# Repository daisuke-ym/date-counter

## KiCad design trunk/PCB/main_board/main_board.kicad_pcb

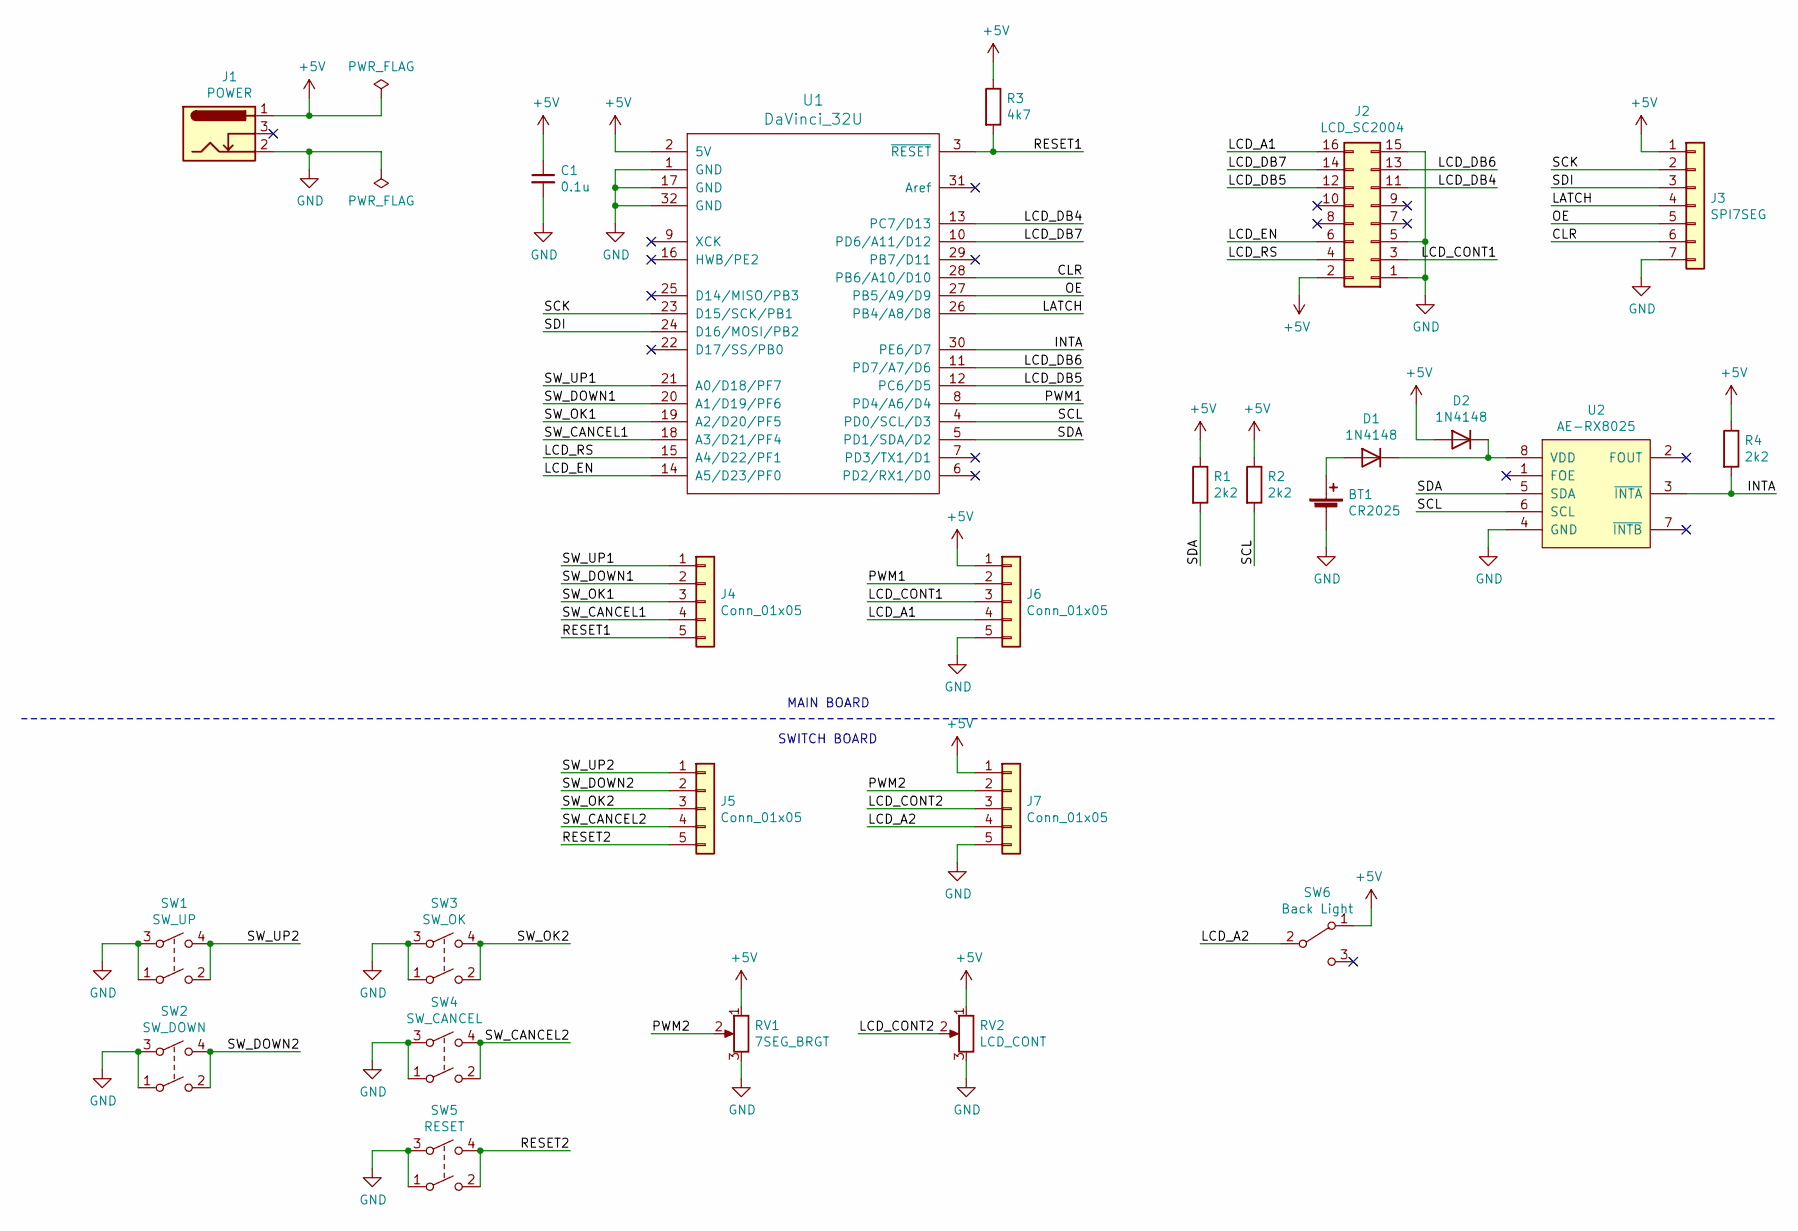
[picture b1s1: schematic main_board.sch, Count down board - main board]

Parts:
BT1: CR2025; CH25-2032LF
C1: 0.1u; C_Disc_D3.4mm_W2.1mm_P2.50mm
D1, D2: 1N4148; D_DO-15_P10.16mm_Horizontal
J1: POWER; BarrelJack_Horizontal
J2: LCD_SC2004; SC2004
J3: SPI7SEG; JST_XH_S7B-XH-A-1_1x07_P2.50mm_Horizontal
J4, J5, J6, J7: Conn_01x05; PinHeader_1x05_P2.54mm_Vertical
R1, R2, R4: 2k2; R_Axial_DIN0207_L6.3mm_D2.5mm_P10.16mm_Horizontal
R3: 4k7; R_Axial_DIN0207_L6.3mm_D2.5mm_P10.16mm_Horizontal
RV1: 7SEG_BRGT; GF063P1
RV2: LCD_CONT; GF063P1
SW1: SW_UP; TVDP01-G73AB
SW2: SW_DOWN; TVDP01-G73AB
SW3: SW_OK; TVDP01-G73AB
SW4: SW_CANCEL; TVDP01-G73AB
SW5: RESET; TVDP01-G73AB
SW6: Back Light; SS12D01G4
U1: DaVinci_32U; DIP-32_W15.24mm_Socket
U2: AE-RX8025; DIP-8_W7.62mm_Socket

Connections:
+5V: C1.1, D2.2 (A), J1.1, J2.2, J3.1, J6.1, J7.1, R1.1, R2.1, R3.1, R4.1, RV1.1, RV2.1, SW6.1 (A), U1.2 (5V)
/CLR: J3.6, U1.28 (PB6/A10/D10)
/INTA: R4.2, U1.30 (PE6/D7), U2.3 (~INTA)
/LATCH: J3.4, U1.26 (PB4/A8/D8)
/LCD_A1: J2.16, J6.4
/LCD_A2: J7.4, SW6.2 (B)
/LCD_CONT1: J2.3, J6.3
/LCD_CONT2: J7.3, RV2.2
/LCD_DB4: J2.11, U1.13 (PC7/D13)
/LCD_DB5: J2.12, U1.12 (PC6/D5)
/LCD_DB6: J2.13, U1.11 (PD7/A7/D6)
/LCD_DB7: J2.14, U1.10 (PD6/A11/D12)
/LCD_EN: J2.6, U1.14 (A5/D23/PF0)
/LCD_RS: J2.4, U1.15 (A4/D22/PF1)
/OE: J3.5, U1.27 (PB5/A9/D9)
/PWM1: J6.2, U1.8 (PD4/A6/D4)
/PWM2: J7.2, RV1.2
/RESET1: J4.5, R3.2, U1.3 (~RESET)
/RESET2: J5.5, SW5.2, SW5.4
/SCK: J3.2, U1.23 (D15/SCK/PB1)
/SCL: R2.2, U1.4 (PD0/SCL/D3), U2.6 (SCL)
/SDA: R1.2, U1.5 (PD1/SDA/D2), U2.5 (SDA)
/SDI: J3.3, U1.24 (D16/MOSI/PB2)
/SW_CANCEL1: J4.4, U1.18 (A3/D21/PF4)
/SW_CANCEL2: J5.4, SW4.2, SW4.4
/SW_DOWN1: J4.2, U1.20 (A1/D19/PF6)
/SW_DOWN2: J5.2, SW2.2, SW2.4
/SW_OK1: J4.3, U1.19 (A2/D20/PF5)
/SW_OK2: J5.3, SW3.2, SW3.4
/SW_UP1: J4.1, U1.21 (A0/D18/PF7)
/SW_UP2: J5.1, SW1.2, SW1.4
GND: BT1.2 (-), C1.2, J1.2, J2.1, J2.5, J2.15, J3.7, J6.5, J7.5, RV1.3, RV2.3, SW1.1, SW1.3, SW2.1, SW2.3, SW3.1, SW3.3, SW4.1, SW4.3, SW5.1, SW5.3, U1.1 (GND), U1.17 (GND), U1.32 (GND), U2.4 (GND)
unnamed: BT1.1 (+), D1.2 (A)
unnamed: D1.1 (K), D2.1 (K), U2.8 (VDD)

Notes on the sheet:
MAIN BOARD
SWITCH BOARD

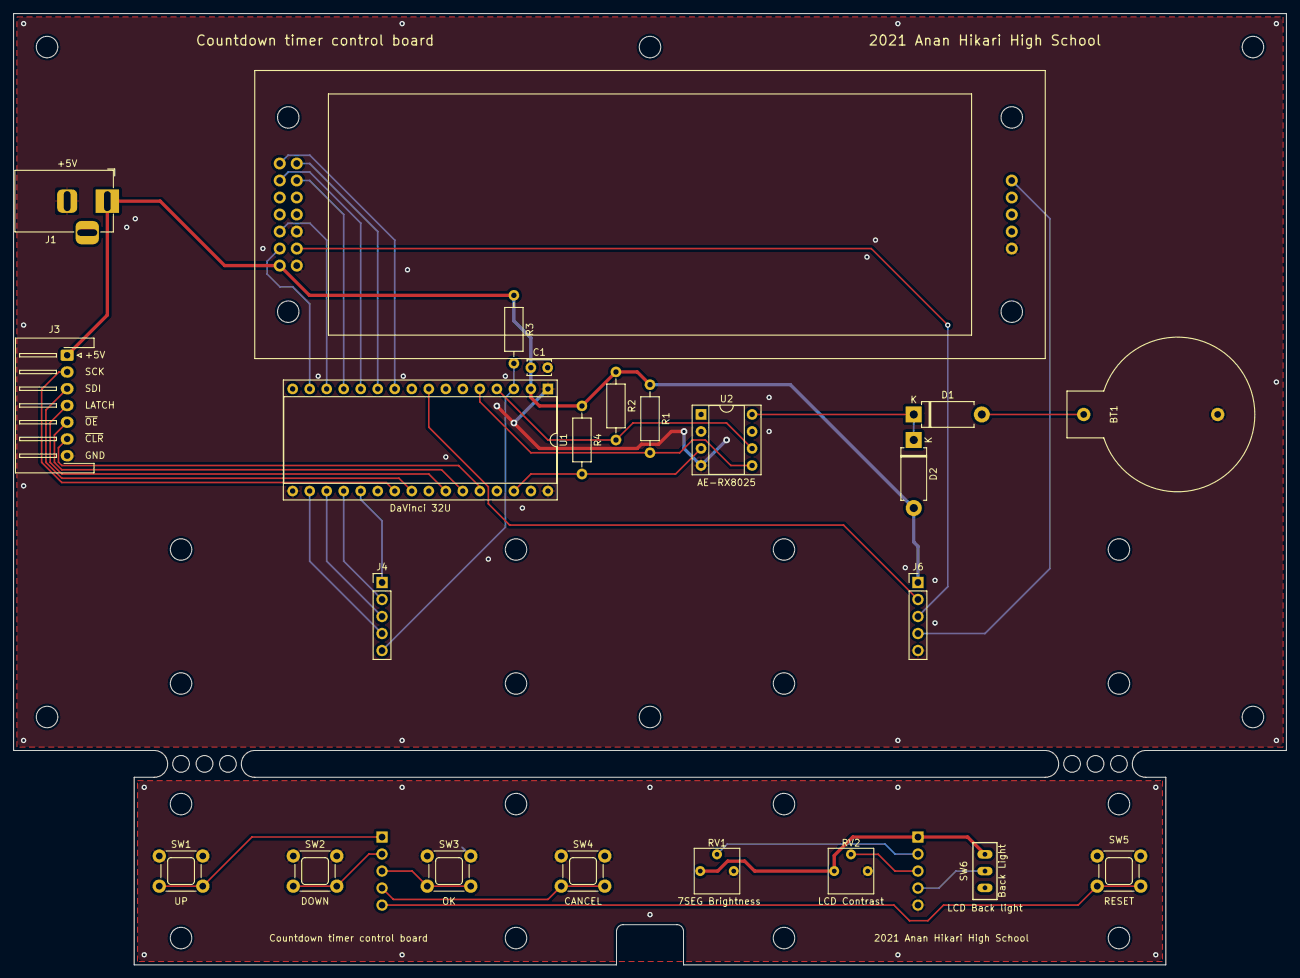
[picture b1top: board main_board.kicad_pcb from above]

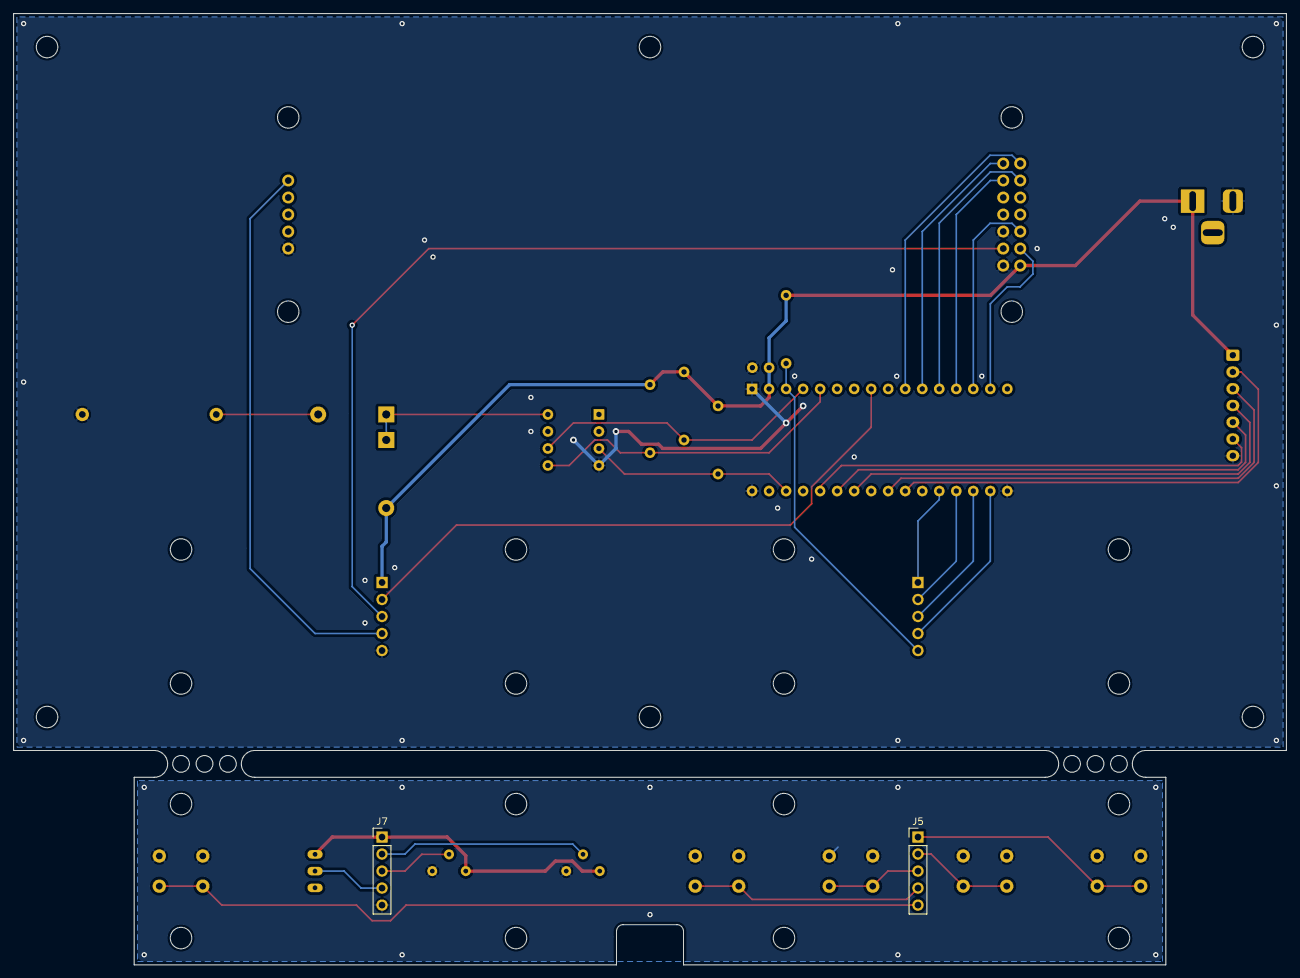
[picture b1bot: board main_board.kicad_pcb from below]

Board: 2 copper layers, 190.0 x 142.0 mm, 25 parts (2 on the bottom side), 34 nets.

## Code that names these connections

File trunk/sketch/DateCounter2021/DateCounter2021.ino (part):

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
// RTCに関する定義
RX8025 rtc; // RX8025  RTC
const uint8_t intAPin = 7; // intA 割り込みピン接続先
volatile boolean AlarmD = false; // アラーム検出か

uint8_t data[7]; // 時刻データやりとり用
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const uint8_t SW_CANCEL = 18; // SW CANCEL-BACK

// 7セグの接続先（SPI）
const uint8_t SDI   = 16; // MOSI
const uint8_t LATCH = 8;  // ラッチ
const uint8_t PWM   = A6;  // 明るさ調整VR用
const uint8_t OE    = 9;  // 明るさ調整PWM用
const uint8_t CLR   = 10; // クリア

// 7セグのフォントデータ
const byte digits[] = {
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
  // 7セグの初期化
  pinMode(SCK, OUTPUT);
  pinMode(SDI, OUTPUT);
  pinMode(LATCH, OUTPUT);
  pinMode(OE, OUTPUT);
  //pinMode(CLR, OUTPUT);
  SPI.begin();
  SPI.setBitOrder(LSBFIRST);
  SPI.setClockDivider(SPI_CLOCK_DIV128);
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
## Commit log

2016-04-15 初期フォルダを作成
2016-04-15 スケッチ保存用のフォルダを作成
2016-04-15 UNO に Big SPI-7Segment 基板を3つとタクトスイッチを4つ繋いで カウントアップとカウントダウンを出来るようにした
2016-04-15 AQM0802 液晶と RX-8025NB RTC の動作テストスケッチ
2016-04-20 BCDからBINへの変換にバグがあった
2016-04-20 RX-8025用ライブラリを追加
    あと何日カウンターのコードを追加（一応完成）
2016-04-25 ケースの設計データを追加（ボトムのみ）
2016-04-27 bottom-case.* を削除した
2016-04-28 回路を収めるケースの設計データを追加
2021-07-07 メインボードの設計データを追加
2021-07-07 カウントダウンタイマー2021のコードを追加
2022-01-24 RTCのバックアップ電源ラインに逆流防止ダイオードが抜けていたのを追加 タクトスイッチのフットプリントが間違っていたのを修正
2022-01-29 取説を追加
